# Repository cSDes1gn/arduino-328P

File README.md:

# Arduino 328P Basic PCB Design

Practice using EAGLE based on guides found here:
https://learn.sparkfun.com/tutorials/using-eagle-schematic/all
https://learn.sparkfun.com/tutorials/using-eagle-board-layout

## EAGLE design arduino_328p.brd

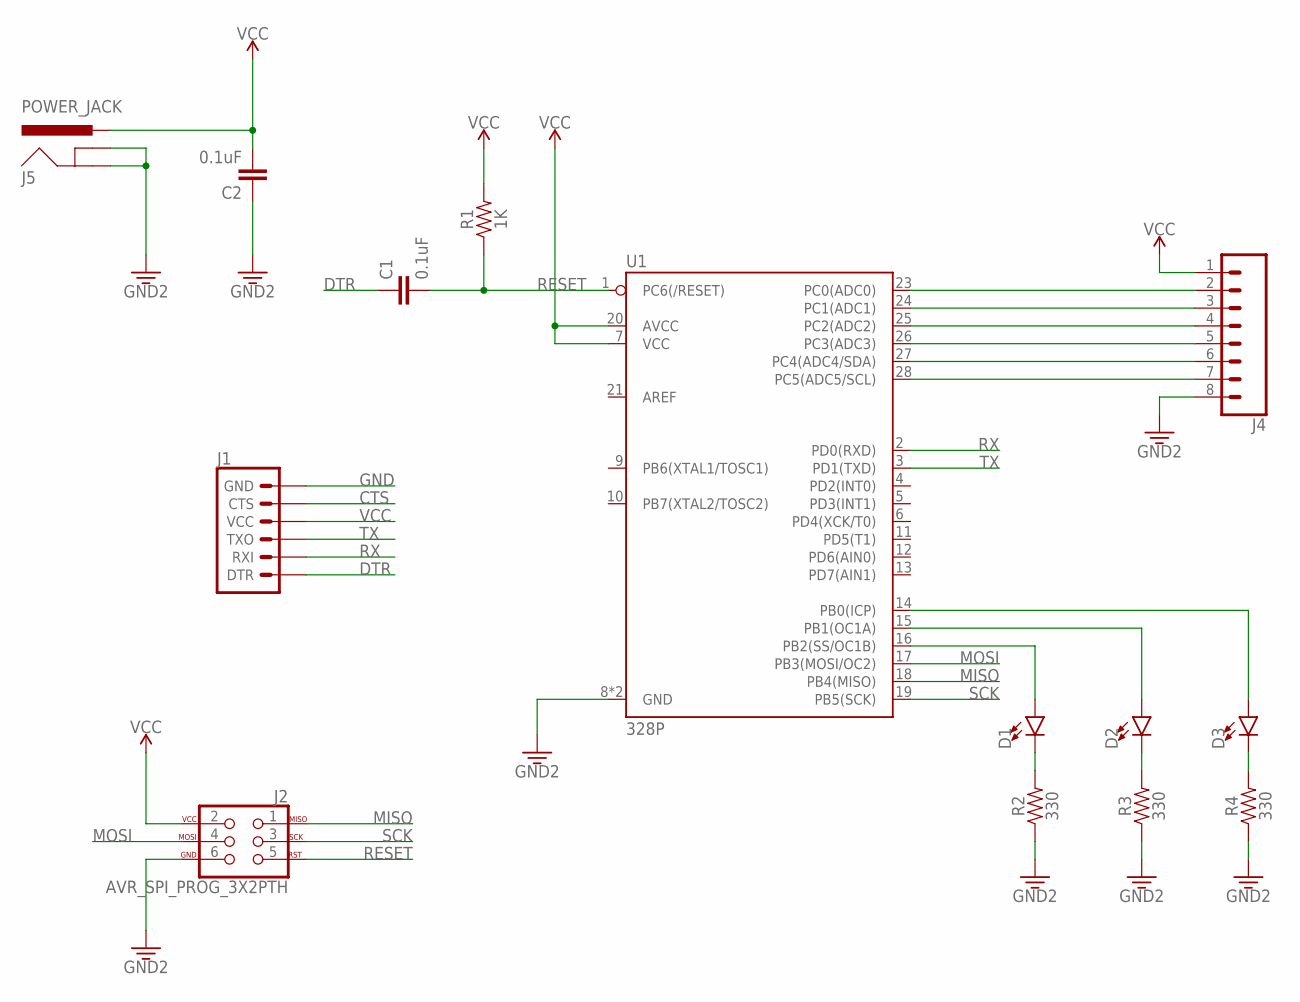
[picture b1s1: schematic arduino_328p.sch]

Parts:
C1, C2: 0.1uF; 0402
D1, D2, D3: LED1206; LED-1206
J1: 6_PIN_SERIAL_TARGETPTH-KIT; 1X06-KIT
J2: AVR_SPI_PROG_3X2PTH; 2X3
J4: CONN_08"; 1X08
J5: POWER_JACK; POWER_JACK_PTH
R1: 1K; 0805
R2, R3, R4: 330; 0805
U1: 328P; DIP28

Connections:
CTS: J1.5 (CTS)
DTR: C1.1, J1.1 (DTR)
GND: C2.1, J1.6 (GND), J2.6, J4.8, J5.GND, J5.GNDBREAK, R2.1, R3.1, R4.1, U1.8 (GND), U1.22 (GND)
MISO: J2.1, U1.18 (PB4(MISO))
MOSI: J2.4, U1.17 (PB3(MOSI/OC2))
unnamed: J4.2, U1.23 (PC0(ADC0))
unnamed: J4.3, U1.24 (PC1(ADC1))
unnamed: J4.4, U1.25 (PC2(ADC2))
unnamed: J4.5, U1.26 (PC3(ADC3))
unnamed: J4.6, U1.27 (PC4(ADC4/SDA))
unnamed: J4.7, U1.28 (PC5(ADC5/SCL))
unnamed: D1.C, R2.2
unnamed: D2.C, R3.2
unnamed: D1.A, U1.16 (PB2(SS/OC1B))
unnamed: D2.A, U1.15 (PB1(OC1A))
unnamed: D3.A, U1.14 (PB0(ICP))
unnamed: D3.C, R4.2
RESET: C1.2, J2.5, R1.1, U1.1 (PC6(/RESET))
RX: J1.2 (RXI), U1.2 (PD0(RXD))
SCK: J2.3, U1.19 (PB5(SCK))
TX: J1.3 (TXO), U1.3 (PD1(TXD))
VCC: C2.2, J1.4 (VCC), J2.2, J4.1, J5.PWR, R1.2, U1.7 (VCC), U1.20 (AVCC)

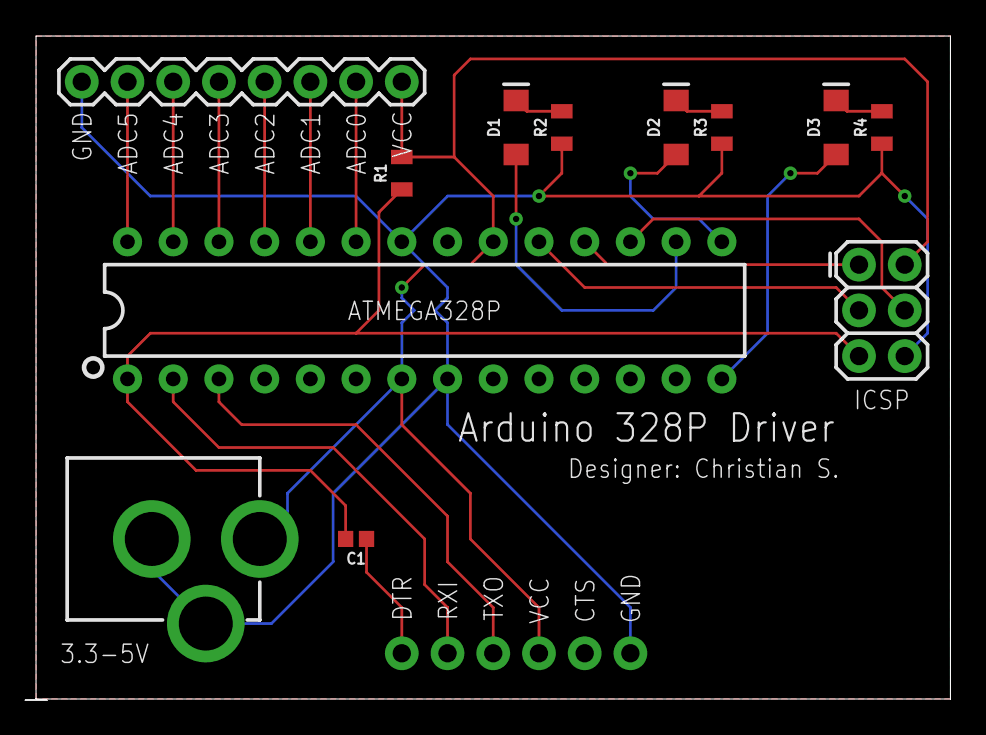
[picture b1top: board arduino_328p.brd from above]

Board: 2 copper layers, 50.8 x 36.8 mm, 14 parts (1 on the bottom side), 21 nets.

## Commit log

2020-12-15 atmega328p wiring
2020-12-16 README
2020-12-17 PCB routing
2020-12-17 copper pours and sikscreen
2020-12-17 replace serial connector
2020-12-17 change current limit resistor to 330
2020-12-25 DRC checks complete

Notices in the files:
parts and their libraries:
SparkFun-Connectors: Licensing: Creative Commons ShareAlike 4.0 International - https://creativecommons.org/licenses/by-sa/4.0
